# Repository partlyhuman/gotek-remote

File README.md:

# Gotek Floppy Emulator Remote Interface

This is a device that relocates the USB, screen, and dial of a Gotek floppy drive emulator (running [FlashFloppy](https://github.com/keirf/flashfloppy)) to a standalone unit you can build yourself. It solves the problem of not having easy access to the drive, for example if your computer's front panel doesn't have a cutout for it. The remote connects to the main unit via a flat flex cable (FFC) which can be threaded through the narrowest of cracks in a desktop chassis, giving you the freedom to place it wherever you prefer.

https://github.com/user-attachments/assets/1192d630-0beb-47c9-abd5-1f5b6c1d0ba6

## Building one

There are two (small) PCBs: One goes inside the Gotek, and the other forms the remote, along with a 3d printed case.

You'll need:

* A Gotek drive with [FlashFloppy](https://github.com/keirf/flashfloppy) installed
* A rotary encoder and 128x32 0.9" OLED screen recommended by [Hardware Mods](https://github.com/keirf/flashfloppy/wiki/Hardware-Mods)
* A USB-A through-hole female connector
* A 10-pin, 0.5mm pitch, straight-through FFC of the desired length (shorter is better)
* Two 10-pin, 0.5mm pitch, SMD FFC connectors
* An electrolytic capacitor for the USB connector, 10uF?
* Some M2 screws
* The two PCBs, fab-ready gerbers are available for the [breakout](pcb/production/gotek-breakout.zip) and [remote](pcb/production/gotek-remote.zip)
* A 3d printed case, print-ready STLs are available for the [top](3dp/Gotek%20Remote_Gotek%20Remote%20Dock%20v20_Case%20Top.stl) and [bottom](3dp/Gotek%20Remote_Gotek%20Remote%20Dock%20v20_Case%20Bottom.stl)
* Optional, a 2x2 right angle female 2.54mm pitch header pin socket
* Optional, two sticky-backed PCB standoffs 

Assembly:

Connect the underlined connections. J8 mirrors the headers mid-board in these revisions of the Gotek, in the same positions, only the underlined connections are needed. J11 goes to the right side of R1 and R2 (in the same order). Make an effort to have these USB jumper wires the same length, and as short as possible. Optionally, J12 goes to the bottom side of the L4 activity LED (replacing the LED). The right-angle connector will make the board slip into place.

Connect the FFC, feed it through the hole left by the screen and out the front of your PC. Hook up the floppy side of things.

When assembling the remote, you'll probably have to desolder the angle pins of the rotary encoder and solder in straight ones. For both the rotary encoder and the OLED screen, the boards will be connected on the right side, so place a spacer on the left side to match height for better support - I use sticky tack. Trim the excess off the header pins for a flush fit.

Assemble the remote in this order:

1. Front side of the case
2. The remote PCB
3. Attach the FFC now before closing the case
4. Rear side of the case, screwing all the layers together
5. Push on rotary shaft cap

I use these options in [ff.cfg](https://github.com/keirf/flashfloppy/wiki/FF.CFG-Configuration-File#options):

* `display-type = oled-128x32-rotate-slow`
* `rotary = half`

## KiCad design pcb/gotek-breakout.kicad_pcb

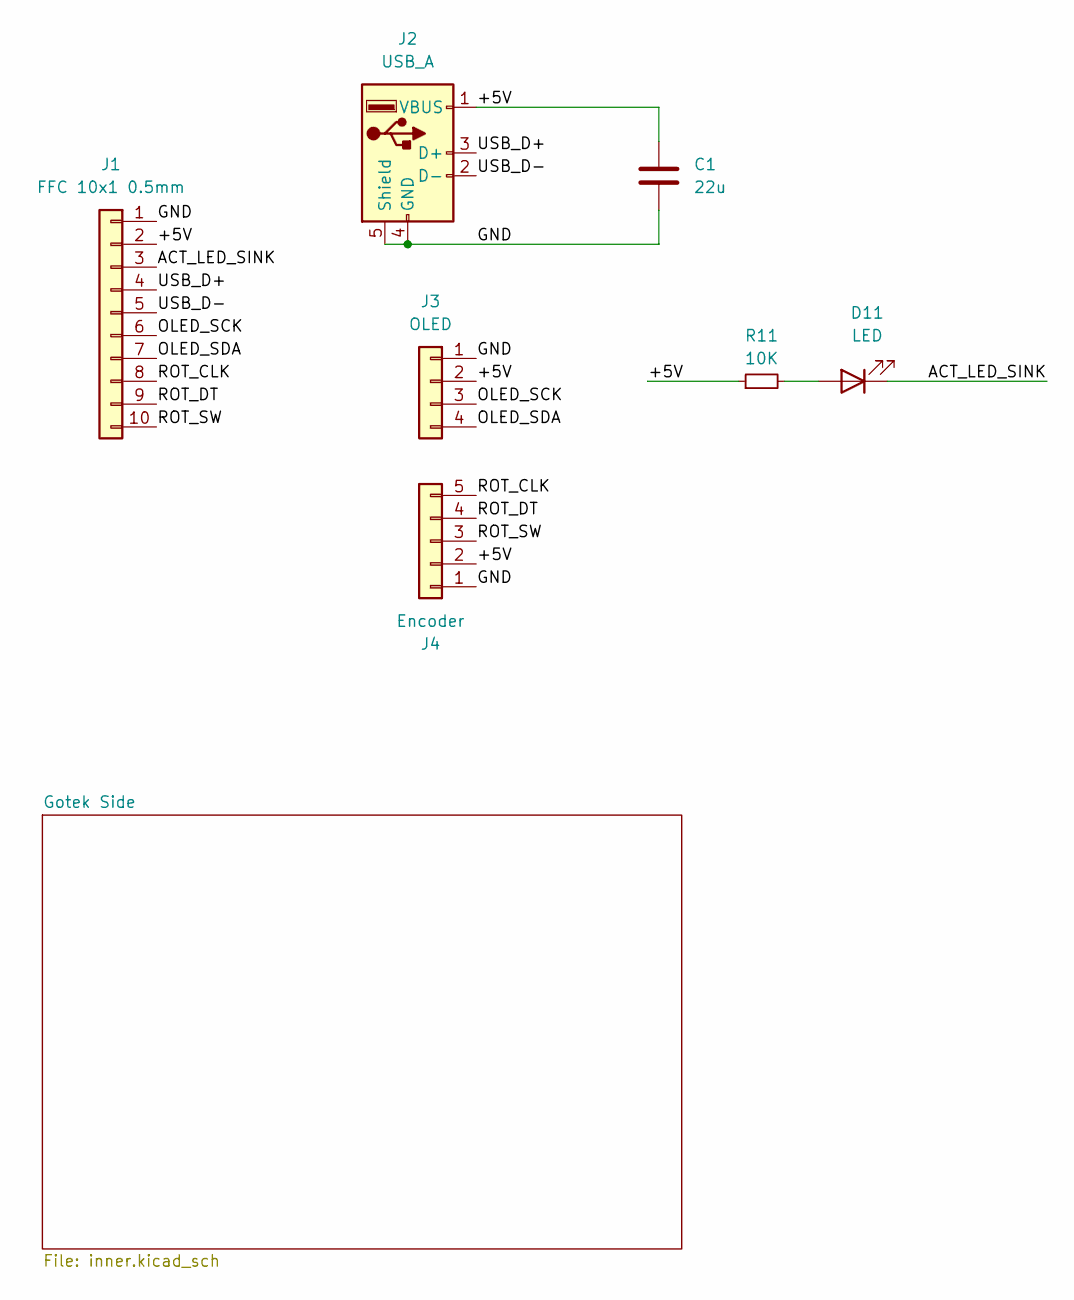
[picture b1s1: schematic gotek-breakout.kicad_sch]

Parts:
C1: 22u; CP_Radial_D5.0mm_P2.50mm
D11: LED; LED_D3.0mm
J1: FFC 10x1 0.5mm; Molex_54548-1071_1x10-1MP_P0.5mm_Horizontal
J2: USB_A; USB_A_Molex_67643_Horizontal
J3: OLED; PinHeader_1x04_P2.54mm_Vertical
J4: Encoder; PinHeader_1x05_P2.54mm_Vertical
R11: 10K; R_Axial_DIN0411_L9.9mm_D3.6mm_P12.70mm_Horizontal

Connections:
/+5V: C1.1, J1.2, J2.1 (VBUS), J3.2, J4.2, R11.1
/ACT_LED_SINK: D11.1 (K), J1.3
/GND: C1.2, J1.1, J2.4 (GND), J2.5 (Shield), J3.1, J4.1
/OLED_SCK: J1.6, J3.3
/OLED_SDA: J1.7, J3.4
/ROT_CLK: J1.8, J4.5
/ROT_DT: J1.9, J4.4
/ROT_SW: J1.10, J4.3
/USB_D+: J1.4, J2.3 (D+)
/USB_D-: J1.5, J2.2 (D-)
unnamed: D11.2 (A), R11.2

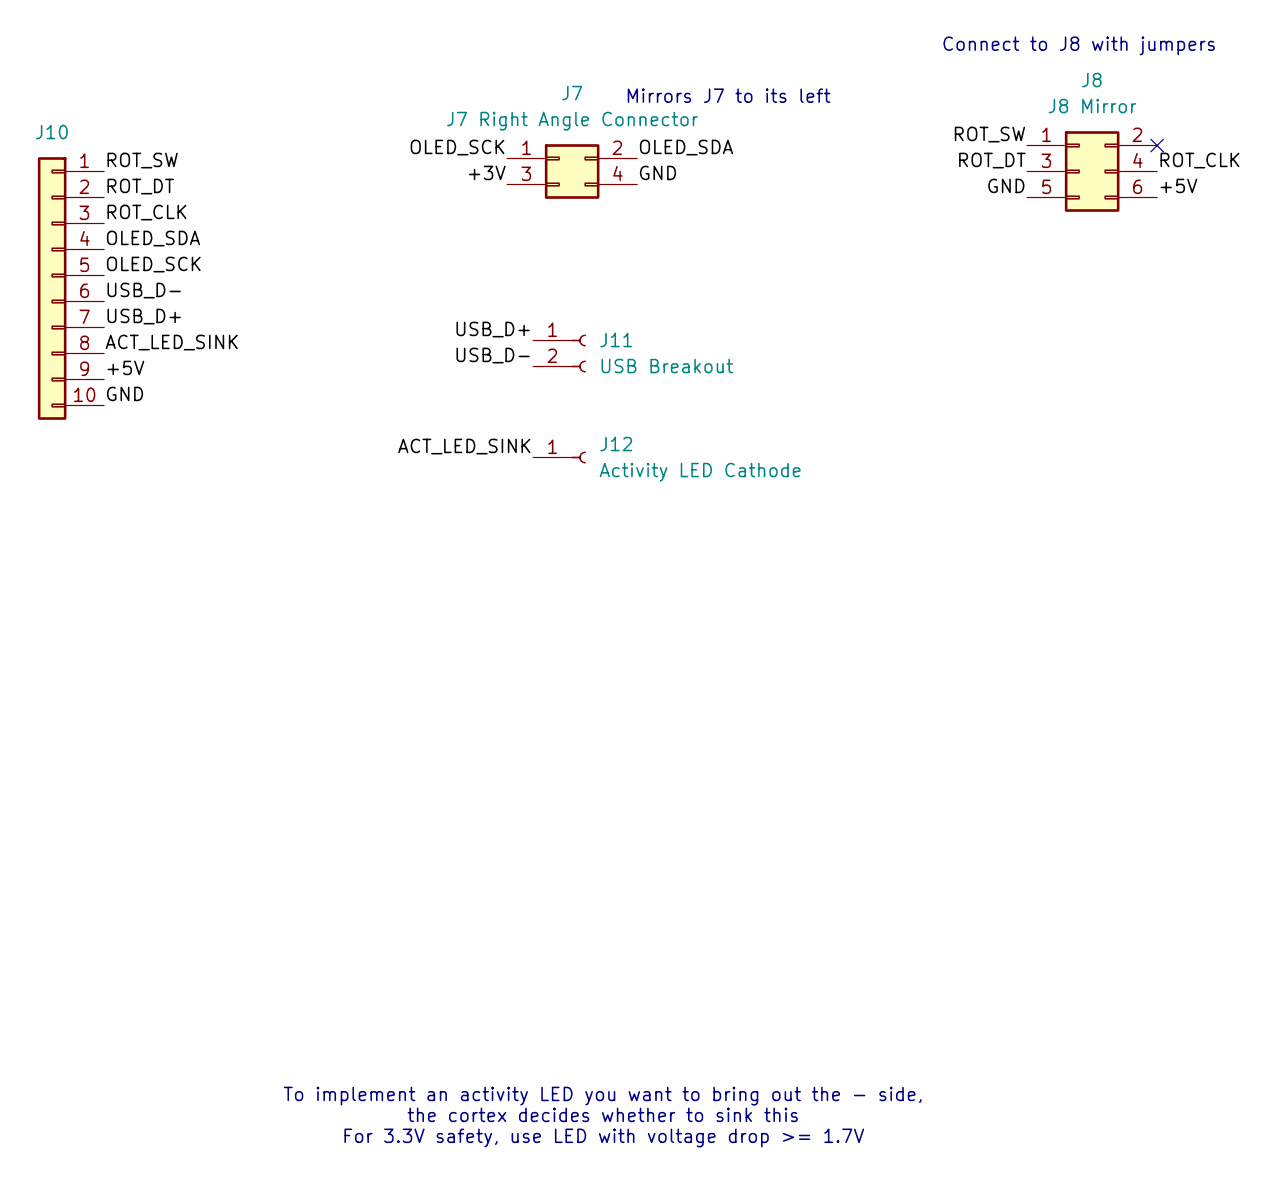
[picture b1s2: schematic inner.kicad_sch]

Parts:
J7: J7 Right Angle Connector; PinHeader_2x02_P2.54mm_Vertical
J8: J8 Mirror; PinHeader_2x03_P2.54mm_Vertical
J10: FFC 10x1 0.5mm; Molex_54548-1071_1x10-1MP_P0.5mm_Horizontal
J11: USB Breakout; PinHeader_1x02_P2.54mm_Vertical
J12: Activity LED Cathode; PinHeader_1x01_P2.54mm_Vertical

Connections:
/Gotek Side/+3V: J7.3
/Gotek Side/+5V: J8.6, J10.9
/Gotek Side/ACT_LED_SINK: J10.8, J12.1
/Gotek Side/GND: J7.4, J8.5, J10.10
/Gotek Side/OLED_SCK: J7.1, J10.5
/Gotek Side/OLED_SDA: J7.2, J10.4
/Gotek Side/ROT_CLK: J8.4, J10.3
/Gotek Side/ROT_DT: J8.3, J10.2
/Gotek Side/ROT_SW: J8.1, J10.1
/Gotek Side/USB_D+: J10.7, J11.1
/Gotek Side/USB_D-: J10.6, J11.2

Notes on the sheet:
Connect to J8 with jumpers
Mirrors J7 to its left
To implement an activity LED you want to bring out the - side, the cortex decides whether to sink this For 3.3V safety, use LED with voltage drop >= 1.7V

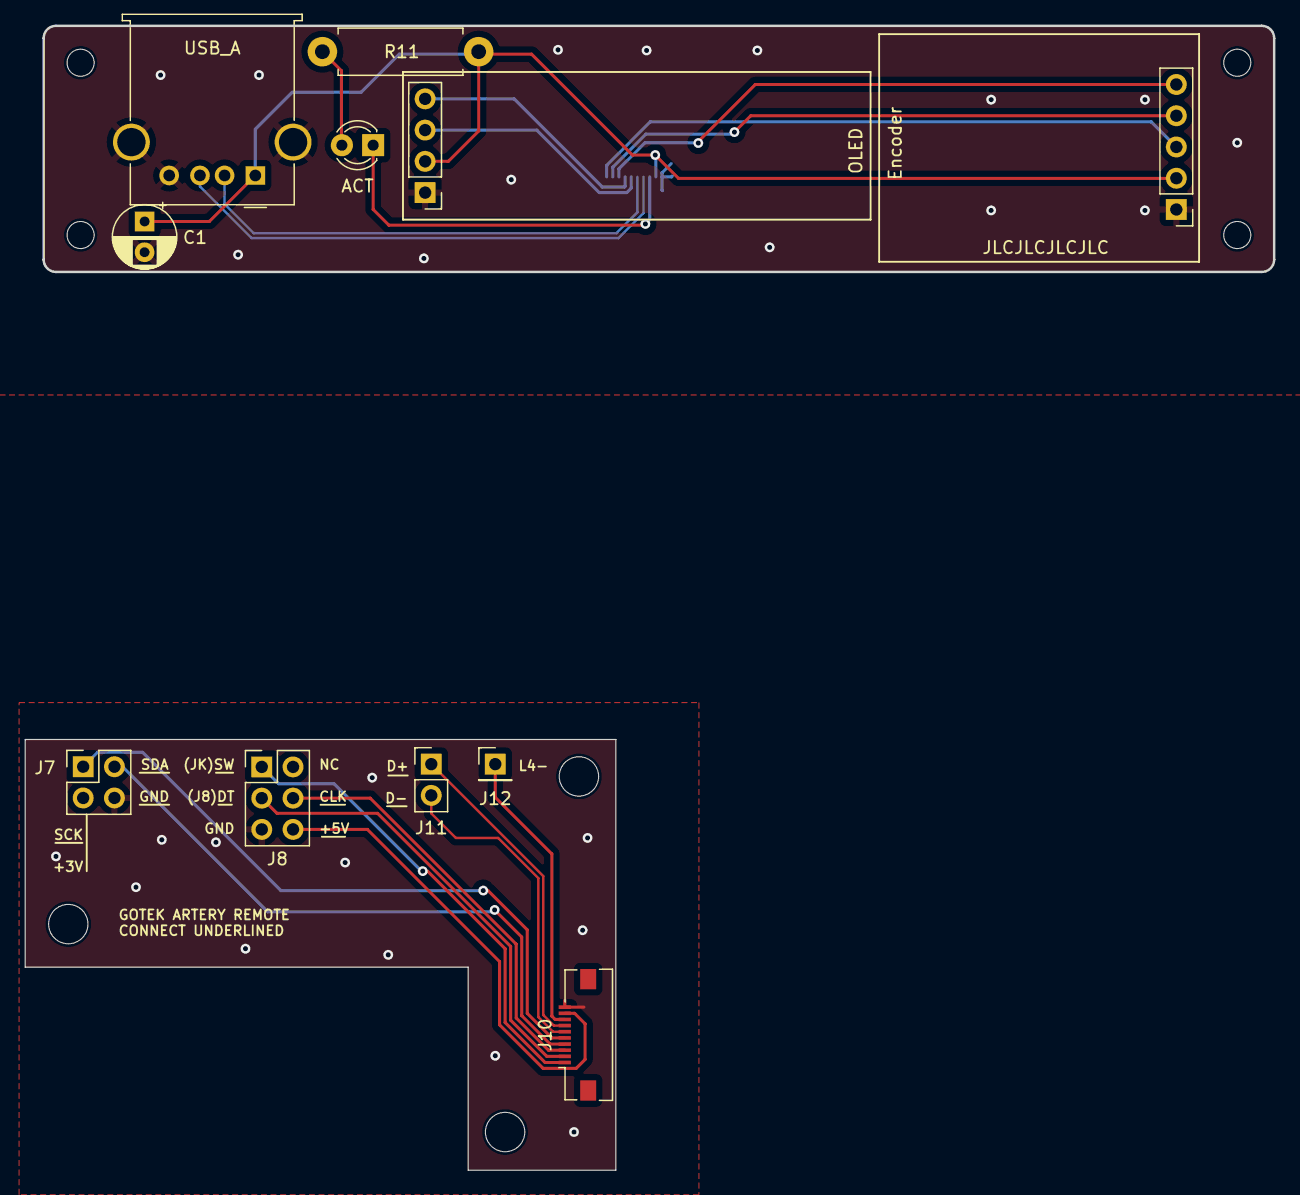
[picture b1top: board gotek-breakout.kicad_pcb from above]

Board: 2 copper layers, 101.5 x 93.0 mm, 19 parts (1 on the bottom side), 21 nets.

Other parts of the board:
H1, H2, H3, H4: MountingHole_2.2mm_M2
H5, H6, H7: MountingHole_3.2mm_M3

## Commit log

2024-03-12 Adds notes
2024-03-12 add gerbers
2024-03-12 Add adapter piece, need to work out mounting
2024-03-12 Breakout board only for newer goteks
2024-03-12 Match D+/D- positions better
2024-03-12 Make room for mounting
2024-03-12 M2 mounting holes to match 3d print
2024-03-12 Add mounting to breakout, update silk
2024-03-12 Add 3d prints
2024-03-12 Readme
2024-03-12 Fix URLs with spaces
2024-03-13 Add license
2024-04-02 Revision 2
2024-04-03 Move FFC up
2024-04-28 Tweaks for rev2
2024-04-28 Nudging items on PCB for rev3
2024-04-28 Updating remote gerbers
2024-04-28 Rev3 print updates
2024-07-15 New photo
